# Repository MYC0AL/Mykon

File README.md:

# Mykon
A modular dev-friendly handheld

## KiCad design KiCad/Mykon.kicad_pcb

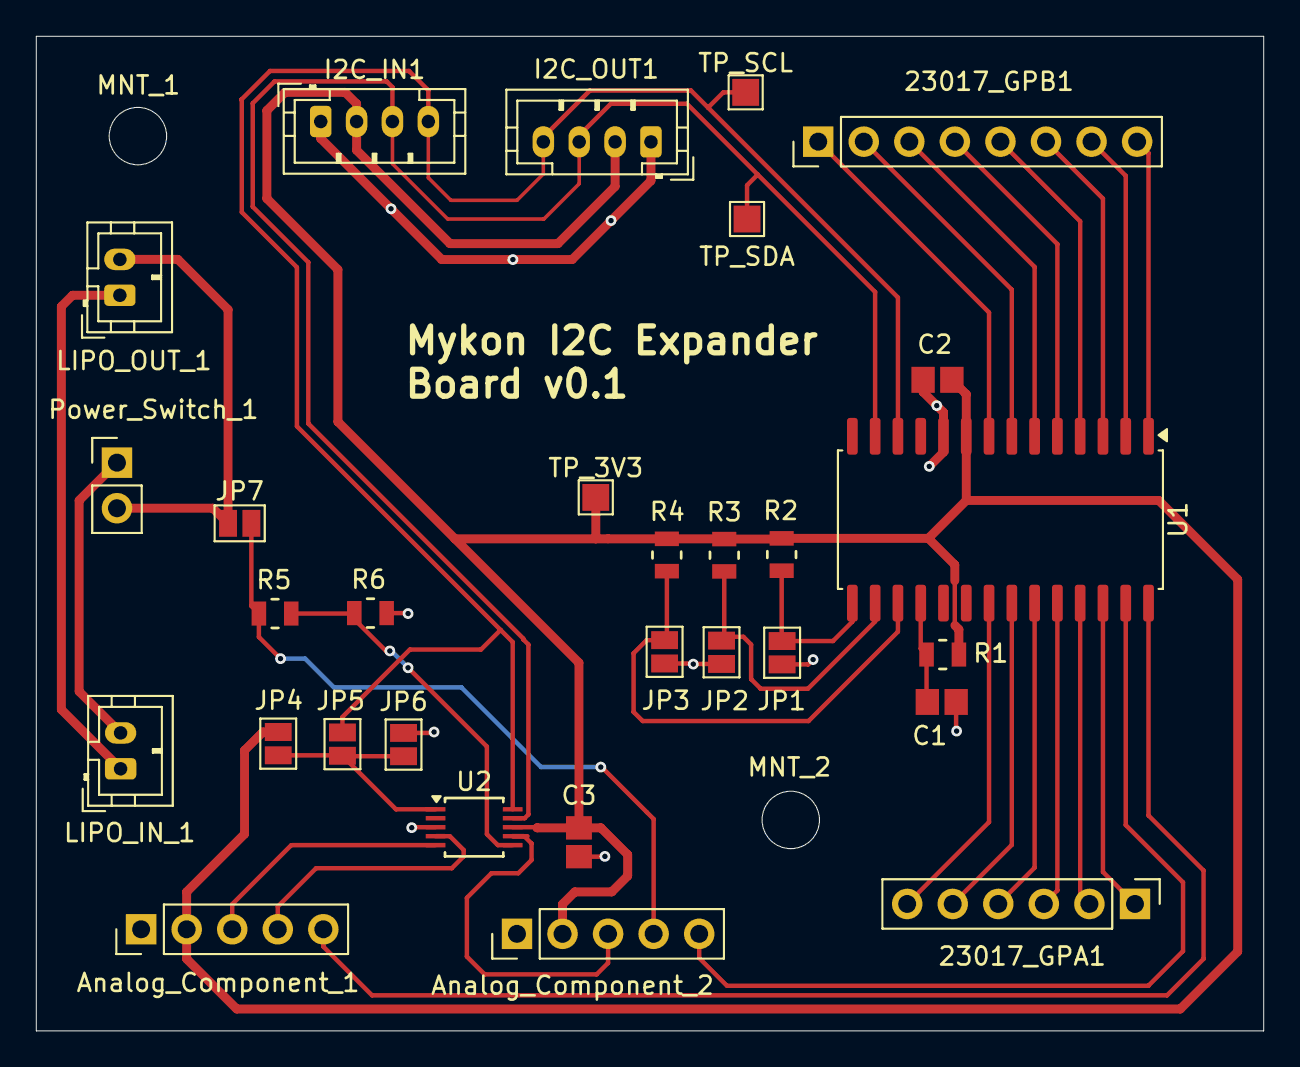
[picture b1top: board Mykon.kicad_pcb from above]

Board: 2 copper layers, 68.4 x 55.4 mm, 32 parts (0 on the bottom side), 33 nets.

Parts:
23017_GPA1: Conn_01x06_Pin; PinHeader_1x06_P2.54mm_Vertical
23017_GPB1: Conn_01x08_Pin; PinHeader_1x08_P2.54mm_Vertical
Analog_Component_1, Analog_Component_2: Conn_01x05_Pin; PinHeader_1x05_P2.54mm_Vertical
C1, C2, C3: 100nF; CAPC220145_88N_KEM
I2C_IN1, I2C_OUT1: Conn_01x04_Pin; JST_PH_B4B-PH-K_1x04_P2.00mm_Vertical
JP1, JP2, JP3, JP4, JP5, JP6, JP7: SolderJumper_2_Open; SolderJumper-2_P1.3mm_Open_Pad1.0x1.5mm
LIPO_IN_1: Conn_01x02; JST_PH_B2B-PH-K_1x02_P2.00mm_Vertical
LIPO_OUT_1: Conn_01x02; JST_PH_B2B-PH-K_1x02_P2.00mm_Vertical
MNT_1, MNT_2: MountingHole_3.2mm_M3
Power_Switch_1: SW_SPST; PinHeader_1x02_P2.54mm_Vertical
R1, R2, R3, R4: 10k; STA_RMCF0805_STP
R5, R6: 100k; STA_RMCF0805_STP
TP_3V3: TestPoint_Pad_1.5x1.5mm
TP_SCL: TestPoint_Pad_1.5x1.5mm
TP_SDA: TestPoint_Pad_1.5x1.5mm
U1: MCP23017_SO; SOIC-28W_7.5x17.9mm_P1.27mm
U2: ADS1115IDGS; TSSOP-10_3x3mm_P0.5mm

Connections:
+3V3: Analog_Component_1.2, Analog_Component_2.2, C2.2, C3.2, I2C_IN1.2, I2C_OUT1.2, JP4.2 (B), R1.1, R2.1, R3.1, R4.1, TP_3V3.1, U1.9 (VDD), U2.8 (VDD)
/SW_ANALOG_1: Analog_Component_1.5, U1.28 (GPA7)
/SW_ANALOG_2: Analog_Component_2.5, U1.27 (GPA6)
/SW_DOWN: 23017_GPA1.5, U1.22 (GPA1)
/SW_HOME: 23017_GPA1.2, U1.25 (GPA4)
/SW_LEFT: 23017_GPA1.4, U1.23 (GPA2)
/SW_RIGHT: 23017_GPA1.3, U1.24 (GPA3)
/SW_UP: 23017_GPA1.6, U1.21 (GPA0)
GND: Analog_Component_1.1, Analog_Component_2.1, C1.2, C2.1, C3.1, I2C_IN1.1, I2C_OUT1.1, JP1.2 (B), JP2.2 (B), JP3.2 (B), JP6.2 (B), R6.1, U1.10 (VSS), U2.3 (GND)
unnamed: 23017_GPA1.1, U1.26 (GPA5)
unnamed: 23017_GPB1.1, U1.8 (GPB7)
unnamed: 23017_GPB1.2, U1.7 (GPB6)
unnamed: 23017_GPB1.3, U1.6 (GPB5)
unnamed: 23017_GPB1.4, U1.5 (GPB4)
unnamed: 23017_GPB1.5, U1.4 (GPB3)
unnamed: 23017_GPB1.6, U1.3 (GPB2)
unnamed: 23017_GPB1.7, U1.2 (GPB1)
unnamed: 23017_GPB1.8, U1.1 (GPB0)
unnamed: Analog_Component_1.3, U2.5 (AIN1)
unnamed: Analog_Component_1.4, U2.4 (AIN0)
unnamed: Analog_Component_2.3, U2.7 (AIN3)
unnamed: Analog_Component_2.4, JP7.2 (B), R5.1
unnamed: JP1.1 (A), R2.2, U1.15 (A0)
unnamed: JP2.1 (A), R3.2, U1.16 (A1)
unnamed: JP3.1 (A), R4.2, U1.17 (A2)
unnamed: JP4.1 (A), JP5.1 (A), JP6.1 (A), U2.1 (ADDR)
unnamed: JP7.1 (A), LIPO_OUT_1.2, Power_Switch_1.2 (B)
unnamed: LIPO_IN_1.1, LIPO_OUT_1.1
unnamed: LIPO_IN_1.2, Power_Switch_1.1 (A)
unnamed: C1.1, R1.2, U1.18 (~RESET)
unnamed: R5.2, R6.2, U2.6 (AIN2)
SCL: I2C_IN1.4, I2C_OUT1.4, JP5.2 (B), TP_SCL.1, U1.12 (SCK), U2.10 (SCL)
SDA: I2C_IN1.3, I2C_OUT1.3, TP_SDA.1, U1.13 (SDA), U2.9 (SDA)

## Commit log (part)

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2026-04-28 Initial commit bringing over ported code
2026-04-29 Added IO and AUDIO tasks
2026-04-30 Figuring out that no pins available
    Adding kicad schematic
2026-05-06 Adding kicad schematic and unfinished pcb
    Determined no extra GPIO on esp32
2026-06-23 Working ADS1115 and MCP23017
2026-06-25 Improved functionality of ADS and MCP
    - Broke SD?
2026-06-26 Added App IO subscription and notifs
    - Fixed SD issue
2026-06-27 Fixed joystick slot machine logic
2026-06-27 Added untested no functionality pong app
2026-06-27 Working Pong App
2026-06-29 Working demo rom emulator
2026-06-30 Working ROM loader from SD card
2026-06-30 Rescaled GB to 480x480
